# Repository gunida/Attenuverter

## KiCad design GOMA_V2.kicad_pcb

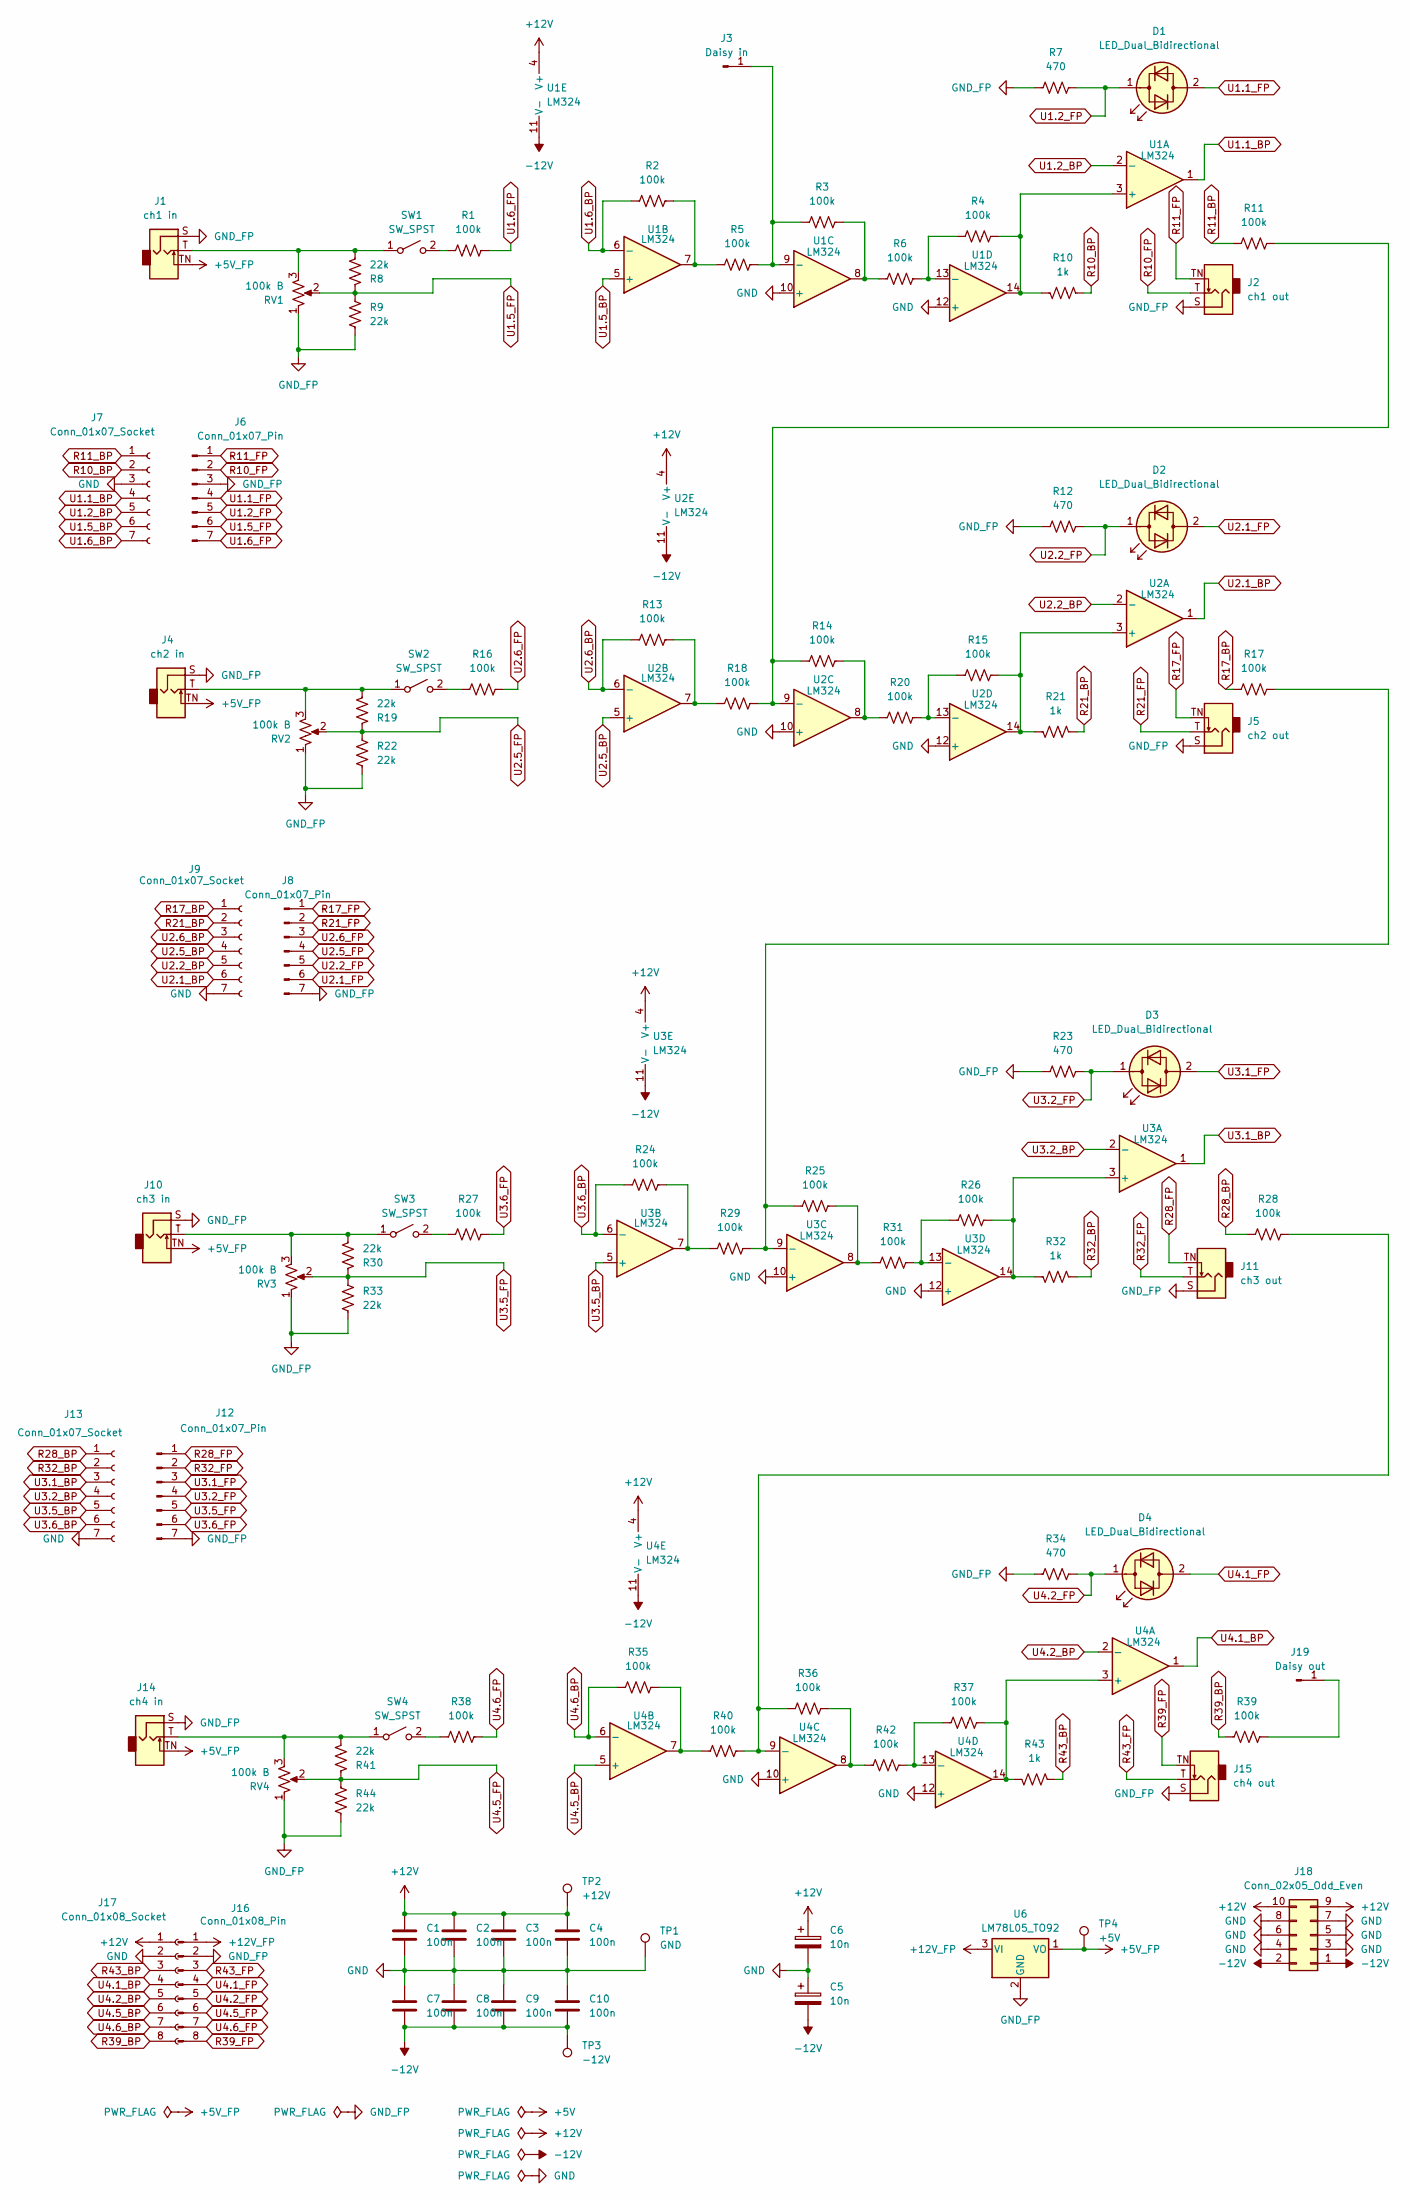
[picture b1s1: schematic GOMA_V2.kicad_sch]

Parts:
C1, C2, C3, C4, C7, C8, C9, C10: 100n; C_Disc_D6.0mm_W2.5mm_P5.00mm
C5, C6: 10n; CP_Radial_D4.0mm_P2.00mm
D1, D2, D3, D4: LED_Dual_Bidirectional; LED_D5.0mm
J1: ch1 in; Thonkiconn mono 3.5mm audio jack PCB spacing
J2: ch1 out; Thonkiconn mono 3.5mm audio jack PCB spacing
J3: Daisy in; PinHeader_1x01_P2.54mm_Vertical
J4: ch2 in; Thonkiconn mono 3.5mm audio jack PCB spacing
J5: ch2 out; Thonkiconn mono 3.5mm audio jack PCB spacing
J6, J8, J12: Conn_01x07_Pin; PinHeader_1x07_P2.54mm_Vertical
J7, J9, J13: Conn_01x07_Socket; PinSocket_1x07_P2.54mm_Vertical
J10: ch3 in; Thonkiconn mono 3.5mm audio jack PCB spacing
J11: ch3 out; Thonkiconn mono 3.5mm audio jack PCB spacing
J14: ch4 in; Thonkiconn mono 3.5mm audio jack PCB spacing
J15: ch4 out; Thonkiconn mono 3.5mm audio jack PCB spacing
J16: Conn_01x08_Pin; PinHeader_1x08_P2.54mm_Vertical
J17: Conn_01x08_Socket; PinSocket_1x08_P2.54mm_Vertical
J18: Conn_02x05_Odd_Even; IDC-Header_2x05_P2.54mm_Vertical
J19: Daisy out; PinHeader_1x01_P2.54mm_Vertical
R1, R6, R11, R16, R17, R20, R27, R28, R31, R38, R39, R42: 100k; R_Axial_DIN0207_L6.3mm_D2.5mm_P2.54mm_Vertical
R2, R3, R4, R13, R14, R15, R24, R25, R26, R35, R36, R37: 100k; R_Axial_DIN0204_L3.6mm_D1.6mm_P2.54mm_Vertical
R5, R18, R29, R40: 100k; R_Axial_DIN0207_L6.3mm_D2.5mm_P10.16mm_Horizontal
R7, R12, R23, R34: 470; R_Axial_DIN0207_L6.3mm_D2.5mm_P10.16mm_Horizontal
R8, R9, R19, R22, R30, R33, R41, R44: 22k; R_Axial_DIN0207_L6.3mm_D2.5mm_P2.54mm_Vertical
R10, R21, R32, R43: 1k; R_Axial_DIN0207_L6.3mm_D2.5mm_P2.54mm_Vertical
RV1, RV2, RV3, RV4: 100k B; Potentiometer_Alpha_RD901F-40-00D_Single_Vertical_3D
SW1, SW2, SW3, SW4: SW_SPST; SMTS 102 SPDT PCB
TP1: GND; TestPoint_Pad_04
TP2: +12V; TestPoint_Pad_04
TP3: -12V; TestPoint_Pad_04
TP4: +5V; TestPoint_Pad_04
U1, U2, U3, U4: LM324; DIP-14_W7.62mm
U6: LM78L05_TO92; TO-92_Inline_Wide

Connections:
+5V_FP: J1.TN, J4.TN, J10.TN, J14.TN, TP4.1, U6.1 (VO)
+12V: C1.1, C2.1, C3.1, C4.1, C6.1, J17.1, J18.9, J18.10, TP2.1, U1.4 (V+), U2.4 (V+), U3.4 (V+), U4.4 (V+)
+12V_FP: J16.1, U6.3 (VI)
-12V: C5.2, C7.2, C8.2, C9.2, C10.2, J18.1, J18.2, TP3.1, U1.11 (V-), U2.11 (V-), U3.11 (V-), U4.11 (V-)
GND: C1.2, C2.2, C3.2, C4.2, C5.1, C6.2, C7.1, C8.1, C9.1, C10.1, J7.3, J9.7, J13.7, J17.2, J18.3, J18.4, J18.5, J18.6, J18.7, J18.8, TP1.1, U1.10 (+), U1.12 (+), U2.10 (+), U2.12 (+), U3.10 (+), U3.12 (+), U4.10 (+), U4.12 (+)
GND_FP: J1.S, J2.S, J4.S, J5.S, J6.3, J8.7, J10.S, J11.S, J12.7, J14.S, J15.S, J16.2, R7.1, R9.1, R12.1, R22.1, R23.1, R33.1, R34.1, R44.1, RV1.1, RV2.1, RV3.1, RV4.1, U6.2 (GND)
unnamed: J3.1, R3.1, R5.2, U1.9 (-)
unnamed: J19.1, R39.1
unnamed: R2.2, R5.1, U1.7
unnamed: R3.2, R6.1, U1.8
unnamed: R13.2, R18.1, U2.7
unnamed: R14.2, R20.1, U2.8
unnamed: R24.2, R29.1, U3.7
unnamed: R25.2, R31.1, U3.8
unnamed: R35.2, R40.1, U4.7
unnamed: R36.2, R42.1, U4.8
unnamed: J1.T, R8.1, RV1.3, SW1.1 (A)
unnamed: R1.1, SW1.2 (B)
unnamed: J4.T, R19.1, RV2.3, SW2.1 (A)
unnamed: R16.1, SW2.2 (B)
unnamed: J10.T, R30.1, RV3.3, SW3.1 (A)
unnamed: R27.1, SW3.2 (B)
unnamed: J14.T, R41.1, RV4.3, SW4.1 (A)
unnamed: R38.1, SW4.2 (B)
unnamed: R4.2, R10.2, U1.3 (+), U1.14
unnamed: R4.1, R6.2, U1.13 (-)
unnamed: R15.2, R21.2, U2.3 (+), U2.14
unnamed: R11.1, R14.1, R18.2, U2.9 (-)
unnamed: R15.1, R20.2, U2.13 (-)
unnamed: R26.2, R32.2, U3.3 (+), U3.14
unnamed: R17.1, R25.1, R29.2, U3.9 (-)
unnamed: R26.1, R31.2, U3.13 (-)
unnamed: R37.2, R43.2, U4.3 (+), U4.14
unnamed: R28.1, R36.1, R40.2, U4.9 (-)
unnamed: R37.1, R42.2, U4.13 (-)
R10_BP: J7.2, R10.1
R10_FP: J2.T, J6.2
R11_BP: J7.1, R11.2
R11_FP: J2.TN, J6.1
R17_BP: J9.1, R17.2
R17_FP: J5.TN, J8.1
R21_BP: J9.2, R21.1
R21_FP: J5.T, J8.2
R28_BP: J13.1, R28.2
R28_FP: J11.TN, J12.1
R32_BP: J13.2, R32.1
R32_FP: J11.T, J12.2
R39_BP: J17.8, R39.2
R39_FP: J15.TN, J16.8
R43_BP: J17.3, R43.1
R43_FP: J15.T, J16.3
U1.1_BP: J7.4, U1.1
U1.1_FP: D1.2 (AK), J6.4
U1.2_BP: J7.5, U1.2 (-)
U1.2_FP: D1.1 (KA), J6.5, R7.2
U1.5_BP: J7.6, U1.5 (+)
U1.5_FP: J6.6, R8.2, R9.2, RV1.2
U1.6_BP: J7.7, R2.1, U1.6 (-)
U1.6_FP: J6.7, R1.2
U2.1_BP: J9.6, U2.1
U2.1_FP: D2.2 (AK), J8.6
U2.2_BP: J9.5, U2.2 (-)
U2.2_FP: D2.1 (KA), J8.5, R12.2
U2.5_BP: J9.4, U2.5 (+)
U2.5_FP: J8.4, R19.2, R22.2, RV2.2
U2.6_BP: J9.3, R13.1, U2.6 (-)
U2.6_FP: J8.3, R16.2
U3.1_BP: J13.3, U3.1
U3.1_FP: D3.2 (AK), J12.3
U3.2_BP: J13.4, U3.2 (-)
U3.2_FP: D3.1 (KA), J12.4, R23.2
U3.5_BP: J13.5, U3.5 (+)
U3.5_FP: J12.5, R30.2, R33.2, RV3.2
U3.6_BP: J13.6, R24.1, U3.6 (-)
U3.6_FP: J12.6, R27.2
U4.1_BP: J17.4, U4.1
U4.1_FP: D4.2 (AK), J16.4
U4.2_BP: J17.5, U4.2 (-)
U4.2_FP: D4.1 (KA), J16.5, R34.2
U4.5_BP: J17.6, U4.5 (+)
U4.5_FP: J16.6, R41.2, R44.2, RV4.2
U4.6_BP: J17.7, R35.1, U4.6 (-)
U4.6_FP: J16.7, R38.2

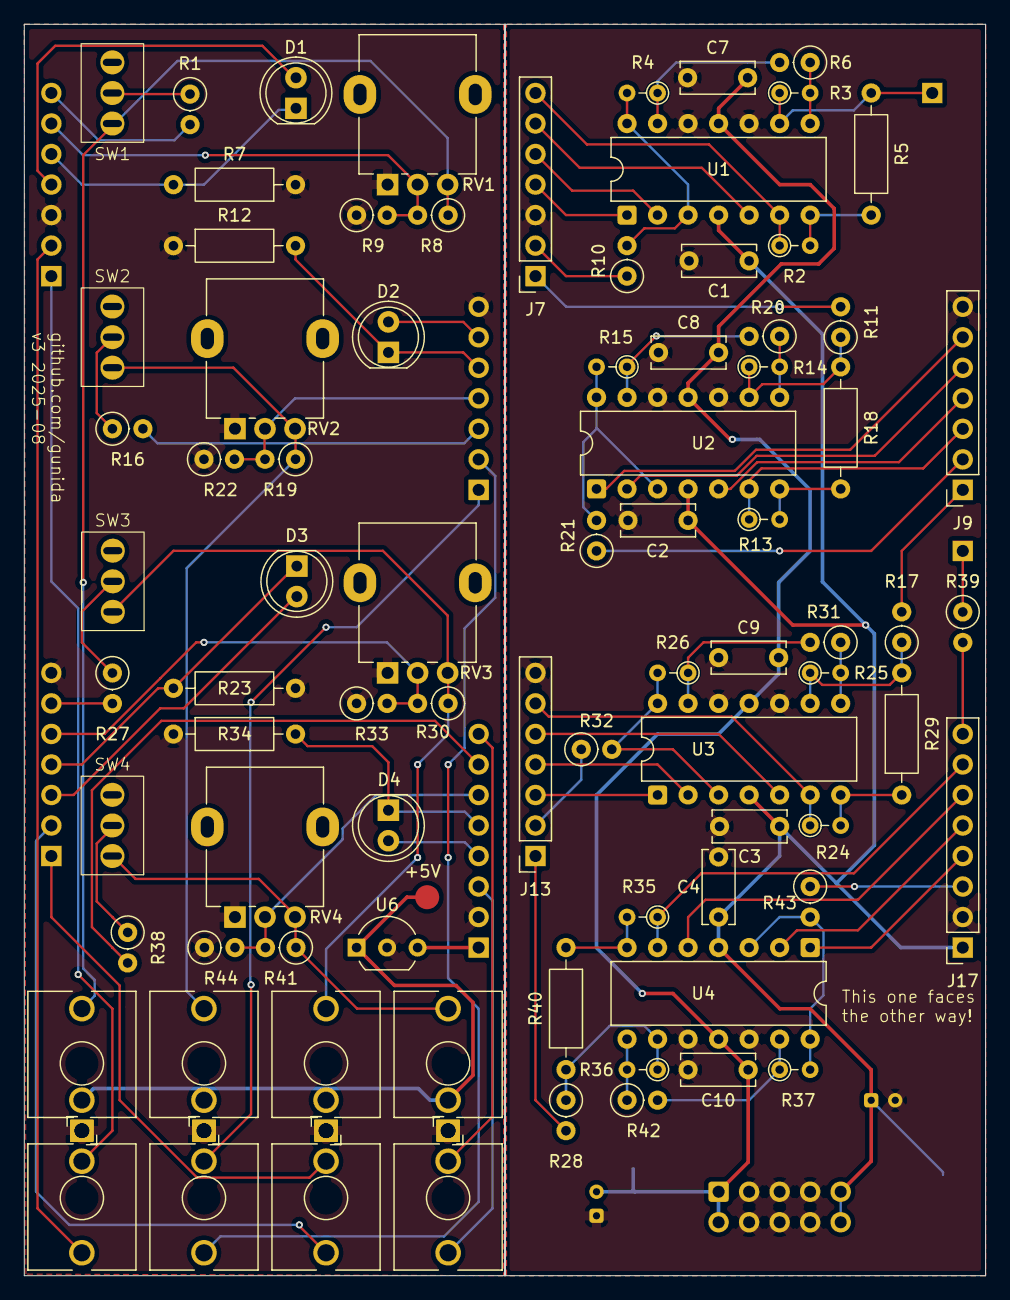
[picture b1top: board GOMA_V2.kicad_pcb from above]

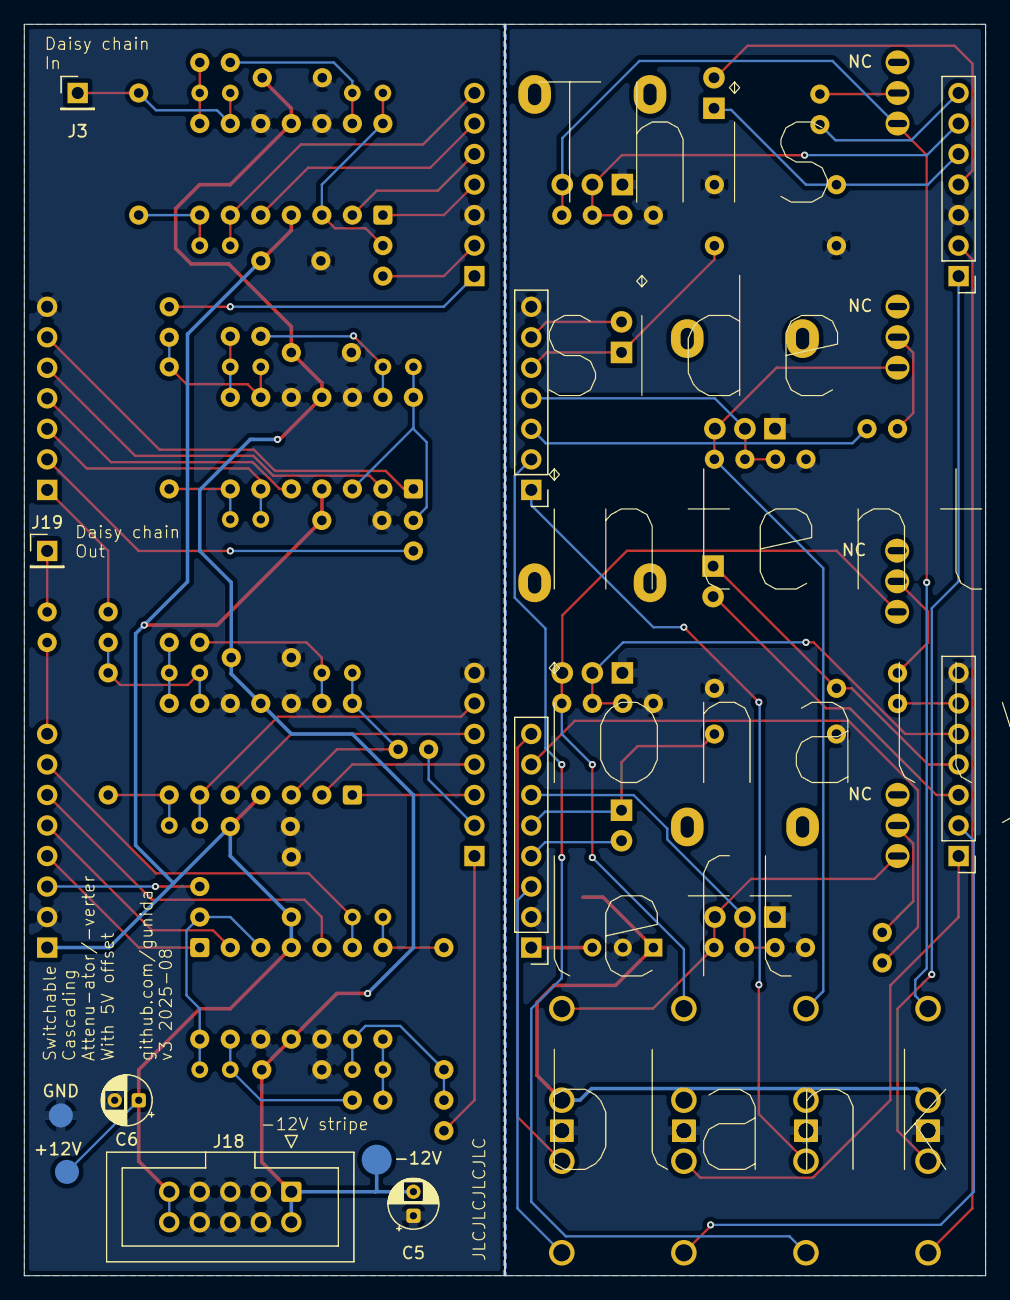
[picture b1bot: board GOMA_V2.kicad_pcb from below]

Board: 2 copper layers, 80.0 x 104.1 mm, 94 parts (12 on the bottom side), 83 nets.

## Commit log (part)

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2025-08-24 gitignore
2025-08-24 v3 design start
2025-08-24 bottom PCB routing
2025-08-25 routing complete, DRC passes
2025-08-25 adjusted component positioning
2025-08-27 added fabrication silkscreen stuff, adjusted positionings
2025-10-19 Added voltage testpoints, front ground fill
2026-03-10 should be no changes
2026-03-10 no changes but git complains
